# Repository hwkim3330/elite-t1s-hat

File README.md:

# Elite T1S HAT

A **10BASE-T1S** board for the **LilyGO T-ETH-Elite** (ESP32-S3), built around
the Microchip **LAN8651** MAC-PHY. It stacks on the Elite's 2×20 header and
gives it a single-pair automotive Ethernet port next to the Elite's own
100BASE-TX (W5500). This board is its own design, not a Raspberry Pi HAT on an
adapter.

**3D:** open [`mechanical/model/t1s_hat.stl`](mechanical/model/t1s_hat.stl) or
[`stack.stl`](mechanical/model/stack.stl) on GitHub to turn it in the browser.
There is also a STEP file for CAD work (`t1s_hat.step`).

| board, top | ground plane (In1) |
|---|---|
|  |  |

| folder | what |
|---|---|
| [`hardware/`](hardware/README.md) | KiCad schematic + **4-layer** PCB (Rev C; Rev B at tag `rev-b`), all generated by `make_t1s_hat.py`; gerbers; JLCPCB BOM/CPL. **[`ORDERING.md`](hardware/ORDERING.md) = how to order.** [`ELECTRICAL.md`](hardware/ELECTRICAL.md) = every value and why |
| [`firmware/`](firmware/README.md) | ESP32-S3 node firmware: LAN8651 over OPEN Alliance TC6 SPI, PLCA, ping/UDP, serial console |
| [`mechanical/`](mechanical/GEOMETRY.md) | outline, holes and header grid, measured from LilyGo's own DXF/3D (`reference/measure.py` re-derives them); `model/` has the 3D models (STL, STEP) and their build and render scripts |

## Status (2026-10-02)

| | |
|---|---|
| Design | **Rev C (4-layer) finished, ready to order**, with the pre-fabrication review fixes of 2026-10-02 (CCOMP, VDDAU, VDDA, RBIAS and crystal parts at their pins; exposed-pad paste clear of the thermal vias; see [`hardware/README.md`](hardware/README.md)). DRC 0 errors / 0 warnings, ERC 0 errors, mechanical error 0.00000 mm against `GEOMETRY.md`, 0 unrouted |
| Parts | every fitted part has an LCSC number, all in stock; **LAN8651 is the scarce one (199 at JLC, 2026-10-01)** |
| Firmware | compiles (Arduino esp32 3.3.0). It ran on a third-party LAN8651 HAT on the same pins (9.5 Mbit/s, PLCA, Zenoh); **not yet on this board, since none has been built** |
| Fabricated | **no.** Order 2–3 first, prove SPI + ping + PLCA between two nodes, then the rest |

What only a real board can settle is listed in
[`hardware/README.md`](hardware/README.md) under "What is NOT verified":
crystal oscillation margin, T1S signal quality and EMC, stack height.

## The short version of the design

- **LAN8651, single 3.3 V** from the Elite's header. The '51 regulates its own
  1.8 V core, so the board has no regulator.
- **Host SPI on the Elite's IO11/9/10, CS on IO8 (header 27), IRQ IO39,
  RESET IO42; 1PPS from DIOA4 on IO40 (header 13) and test pad TP1.** Rev C
  and the TSN Lab HAT put CS on header 24 (IO0, the BOOT strap) as a Pi HAT
  would; Rev D moved it off the strap. The firmware finds CS on either pin.
- **Bus side per AN1718:** common-mode choke → 100 nF DC block → termination
  (fit per bus position: 49R9 end / 1K5 drop) → optional ESD → 4-pin 2.54 mm push-in (Rev D)
  terminal block, wired P N N P so a node taps a daisy chain.
- **4 layers (since Rev B):** signals on top, In1 solid GND, In2 +3V3, bottom only three SPI escapes. The T1S pair is 50 Ω by construction (0.35 mm over 0.21 mm of prepreg). Rev A, the 2-layer version, is in git history.

## Where it is used

A networking test bench: ESP32-S3 nodes running Zenoh-pico behind two
TSN switches with FRER (IEEE 802.1CB). The nodes use the Elite's
own W5500 today; this HAT gives them a 10BASE-T1S edge link, and its firmware's
bridge mode joins a T1S segment to the switched 100BASE-TX backbone.

## History

Started as a sub-folder of an earlier adapter project (a Raspberry Pi HAT
carrier for the Elite) and split out on 2026-09-28 with its history, because the
board is its own product.

## License

MIT for everything written here; third-party parts keep their own licences
(listed in [`LICENSE`](LICENSE)).

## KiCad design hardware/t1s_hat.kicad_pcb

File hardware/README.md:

# T1S HAT — LAN8651 10BASE-T1S for the LilyGO T-ETH-Elite

Our own 10BASE-T1S board for the [LilyGO
T-ETH-Elite](https://github.com/Xinyuan-LilyGO/LilyGO-T-ETH-Series)
(ESP32-S3), built around a **Microchip LAN8651** MAC-PHY. It replaces buying
TSN Lab's ready-made HAT: same chip, same host header, our schematic.

Two source files govern this board and **nothing here re-derives a number in
either of them**:

| file | governs |
|---|---|
| [`ELECTRICAL.md`](ELECTRICAL.md) | every component, value and pin-handling rule, each quoted from Microchip DS60001734F or AN1718 (DS60001718D) |
| [`../mechanical/GEOMETRY.md`](../mechanical/GEOMETRY.md) | outline, mounting holes, 2×20 grid — measured from LilyGo's own DXF and 3D CAD |

Everything is generated by [`make_t1s_hat.py`](make_t1s_hat.py), which emits
the symbol library, the three project-local footprints, the schematic and the
PCB, then reads the board back and asserts every mechanical feature against
`GEOMETRY.md`.

**This is Rev D (2026-10-07): Rev C with a push-in spring terminal for the bus** -- Kefa KF141R-2.54-4P
(press the lever, push the wire in) instead of the 3.81 mm pluggable Phoenix header that needed a mating
plug. Two review bugs fixed with it:

| Rev C | Rev D | why |
|---|---|---|
| CS_N on header 24 = **IO0, the ESP32-S3's BOOT strap** | CS_N on header **27 = IO8** (free on the Elite); R5 pull-up kept | pressing BOOT on a live node asserted CS mid-transaction; any glitch on the strap at reset could also start the ROM loader |
| DIOA0…4 all to ground | **DIOA4 (pin 23) = 1PPS** to test pad **TP1** and header **13 = IO40**; DIOA0…3 still to ground | the LAN8651 has a dedicated 1PPS output on DIOA4 (PPSCTL); with DIOA grounded there was no way to see the 1588 clock on a scope, so PTP accuracy could not be measured, only precision |

PPS leaves pin 23 through a via just past its pad (F.Cu there is C4/C5 and the VDDAU lane) and runs on
B.Cu, which is empty in that area, to TP1 and the header. R5's +3V3 via moved 1 mm left to make room for
CS. DRC 0, ERC 0 errors (6 warnings, was 7: DIOA4 is no longer tied to ground), JLC CPL check exact.
Rev C is at git tag `rev-c`.

**Rev C (2026-10-01, review fixes 2026-10-02), 4-layer: the design is
finished and ready to order.** Rev C is Rev B without the status LEDs and with
VDDA rerouted; an independent review before fabrication then moved the CCOMP,
VDDAU, VDDA and RBIAS parts and the crystal next to their pins and split U1's
exposed-pad paste (see "Rev C" below). It has not been ordered yet.
Rev B is at git tag `rev-b`. Rev A was 2-layer; its layout notes (the single-layer
crossings, JP1, the 3V3 rail) are in git history before commit "Rev B".

## What it is

- **LAN8651**, 32-VQFN 5×5, single 3.3 V rail (the '51 regulates its own 1.8 V
  core, so there is no second regulator and no sequencing diode).
- **OPEN Alliance TC6 SPI** to the host on the same header pins TSN Lab's
  device-tree overlay uses, so their SDK and the mainline `microchip,lan8651`
  driver both work unmodified if this board is ever put on a Pi.
- **Bus interface network** in AN1718's MINIMAL BIN order: common-mode choke →
  AC coupling caps → termination → ESD → 4-way 2.54 mm push-in spring terminal (Rev D; Rev C: 3.81 mm pluggable)
  block, wired so the node taps a daisy chain.
- **4 layers:** signals on top, In1.Cu solid GND, In2.Cu +3V3, bottom only the
  three SPI escapes. The T1S pair is 50 Ω by construction.
- 34 parts, 4 of them deliberately unstuffed (R1/R2 termination, MOV1/MOV2 ESD).

## The two parts that had to be chosen, not assumed

Both are drawn from their own data sheet into
[`fp/t1s_hat.pretty`](fp/t1s_hat.pretty), generated by `make_t1s_hat.py`
alongside the board, and the generator asserts the pad count and the overall
land size back out of the finished `.kicad_pcb`.

### L1 — TDK **ACT1210L-201-2P-TL00**, LCSC **C131444**

AN1718 names ACT1210D-131-2P-TL00, ACT1210E-241-2P-TL00 and Murata
DLW32MH241MX2, and says in the same breath that *"exact component part numbers
and parameters must be determined by the customer's unique application
requirements"* — they are examples. All three are **3.2 × 2.5 mm** (EIA 1210)
2-line chokes in the 130…240 µH @ 100 kHz band. The board previously sat on
KiCad's `Inductor_SMD:L_CommonMode_Wurth_WE-CNSW-1206`, a **3.2 × 1.6 mm**
land: same length, 0.9 mm too narrow, so the real part's terminals miss the
pads. KiCad ships no 4-terminal common-mode choke land in 3225.

The part fitted instead is the **ACT1210L-201-2P-TL00**: same ACT1210 package,
200 µH @ 100 kHz — inside the span AN1718's own examples cover — 70 mA,
5.5 Ω, AEC-Q200, and, unlike all three examples, **stocked at LCSC**
(C131444, ~$0.39/1k), which is where this board gets built.

Its land is `t1s_hat:L_CommonMode_TDK_ACT1210_3225`, drawn from TDK's ACT1210
data sheet "Layout recommendation" (drawing IND1512-9): **4.1 mm overall
across the pads with a 2.0 mm gap between the columns**, so each pad is
1.05 mm long on a 3.05 mm pitch, and **1.6 mm overall across the rows with a
0.4 mm gap**, so each pad is 0.60 mm wide on a 1.0 mm pitch. Body from the
same sheet: 3.2 ±0.2 long, 2.5 ±0.2 wide, 3.9 max over the terminals.

The symbol changed with it: the ACT1210's windings are **1-4 and 2-3**
(pin configuration and circuit diagram, same sheet), which is
`Device:L_Coupled_1423`, not the `…_1243` the 1206 Würth part needed.

### MOV1 / MOV2 — TDK **AVRH10C221KT1R5YA8**, LCSC **C2157827**

This is the part `ELECTRICAL.md` already names, and it is a **1005 [0402]**
chip varistor — 1.0 × 0.5 × 0.5 mm, 220 V V1mA, 70 V DC, **1.5 pF**, 25 kV per
IEC 61000-4-2. The board had it on `Resistor_SMD:R_1206_3216Metric`: three
size codes too big. It is now on `t1s_hat:Varistor_TDK_AVRH10_1005`, from the
recommended land pattern in TDK's automotive AVR chip-varistor catalogue
(pad 0.35…0.45 long, gap 0.3…0.5, pad 0.4…0.6 wide — the middle of each:
**0.40 long, 0.40 gap, 0.50 wide**). KiCad's `R_0402_1005Metric` is 0.54 ×
0.64 on a 1.02 mm pitch, outside all three ranges, which is why this one is
drawn here too. Both parts stay **DNP**; the land is now a real one.

## Rev B layout — what four layers bought

| | Rev A (2-layer) | Rev B (4-layer) |
|---|---|---|
| 3V3 | a rail round three sides of the board | **In2.Cu plane**, one via beside every 3V3 pad; no 3V3 trace exists |
| GND | B.Cu pour, one via per decoupling cap | **In1.Cu plane with no tracks at all**, plus F.Cu and B.Cu pours |
| VDDP pin 17 | 84 mm lap of the board through a 0 Ω jumper (JP1) | own ferrite-option island **FB4**, 0.01 + 0.1 µF at the pin |
| VDDP pin 7 | caps 7 mm away at the end of a column | C8 then C7 straight off the pin, FB3 behind them |
| SPI | MOSI looped out to the board edge and back; MISO ran between R5's pads | 2.5 mm fan-out: MISO/CS/SCLK drop through one via each to B.Cu, MOSI/IRQ/RESET stay on F.Cu, none crosses |
| T1S pair | 0.35 mm over 1.51 mm of FR4 — nowhere near 50 Ω | 0.35 mm over 0.21 mm of prepreg — **50.1 Ω** |

The rules the layout was held to, each checked by the generator or DRC:

- **In1.Cu and In2.Cu carry no tracks** (`plane tracks: 0`). Nothing slots the
  reference plane under the pair; the only cuts are the choke void AN1718
  asks for and the antenna window.
- **Every bus trace from the choke to CN1 is 0.35 mm** (`pair width` row).
- **Nothing passes between two vias.** The QFN's 0.5 mm pitch cannot fit a
  0.45 mm via plus 0.2 mm clearance each side with a track between, so the
  three B.Cu escapes are fanned out to a 1.1 mm pitch row first.
- **The B.Cu escapes turn right at staggered heights** (9 / 10 / 11 mm) and
  enter the header between pad columns, never across one of the Elite's
  pins that this board does not use.
- **The pull-ups cost no vias of their own:** R4 and R6 sit in-line on their
  F.Cu signal, and R5 sits on the CS lane to header pin 27 (pin 24 before Rev D).

## Two decisions that are not in ELECTRICAL.md / GEOMETRY.md

### 1. No RJ45 notch — the outline is a plain rectangle

`GEOMETRY.md`'s notch exists because a board ~13 mm above the Elite would foul
the RJ45, which stands 15.97 mm. This board is lifted clear of the jack by a
taller riser instead, so nothing has to be cut away. Outline is the full
**66.22 × 49.19 mm rectangle, 3 mm corners**. Everything else mechanical in
`GEOMETRY.md` is unchanged and still authoritative: the four asymmetric
mounting holes and the 2×20 grid.

### 2. The connection is two-stage — read this before ordering parts

```
   T1S HAT  (this board)
        ↑ its 2x20 socket goes on the riser's long pins
   ── 2x20 stacking riser ──          ≈23 mm total (calculated), set by the riser
        ↑ riser socket swallows the Elite's own 9.30 mm pins
        ↑ RJ45 (15.97 mm) passes beside the stack, not through a notch
   LilyGO T-ETH-Elite (ESP32-S3)
```

**A single tall stacking header does not work here.** The Elite's pins are
only 9.30 mm long; they would reach barely halfway up a ~17 mm barrel whose
contacts sit near the top. You need a **riser** (a 2×20 stacking header that
plugs onto the Elite and presents longer pins) plus this board's **socket**.
That is a real failure mode someone will otherwise hit at the checkout page.

Board height above the Elite PCB is **≈23 mm, calculated** from the parts in
`ORDERING.md` (riser body 8.3 + ~6 mm of pin inside J1 + J1's 8.5 body), and set by the riser.
Nothing on this board depends on the exact number.

## Stack-up

JLCPCB **JLC04161H-7628**, 1.6 mm, written into the board file:

| layer | | thickness |
|---|---|---|
| F.Cu | signals, parts, GND flood | 0.035 mm (1 oz) |
| prepreg | 7628, εr 4.4 | 0.2104 mm |
| In1.Cu | **GND plane, no tracks** | 0.0152 mm (0.5 oz) |
| core | FR4 | 1.065 mm |
| In2.Cu | **+3V3 plane, no tracks** | 0.0152 mm (0.5 oz) |
| prepreg | 7628, εr 4.4 | 0.2104 mm |
| B.Cu | three SPI escapes + GND pour | 0.035 mm (1 oz) |

50 Ω single-ended on F.Cu over In1.Cu, IPC-2141:
Z0 = 87 / √(4.4 + 1.41) · ln(5.98 · 0.2104 / (0.8 · 0.35 + 0.035)) = **50.1 Ω**.
JLC's own calculator for this stack-up is the one to trust if it disagrees; ask
for impedance control when ordering and they will test it.

Design rules: 0.2 mm clearance (netclass), 0.15 mm minimum track, 0.45 mm vias
with 0.25 mm drill, 0.20 mm minimum drill (the QFN's thermal vias), and one
custom rule in `t1s_hat.kicad_dru`: **BUS_P/BUS_N keep 0.45 mm from every other
net** (pads, tracks, vias and the F.Cu flood). The one exception is inside each
MOV, whose own data-sheet land puts its BUS and GND pads 0.40 mm apart (the rule file relaxes clearance to 0.15 mm between pads inside each MOV courtyard, which covers that 0.40 mm gap).

## Termination stuffing — the one thing an assembler must decide

The board **ships with R1/R2 unstuffed**, per `ELECTRICAL.md` ("footprints
fitted, DNP by default — stuff per where this node sits on the bus"). The
silkscreen carries the table:

| where this node sits | R1, R2 |
|---|---|
| **end of the bus** | 49R9 1 % 1206 (AN1718: 1 W; the JLC variant fits 0.75 W — ORDERING.md) |
| **interior drop node** | 1K5 1 % 1206 |

`R3` (100 k) and `C3` (100 nF) — AN1718's common-mode termination — **are
fitted**. ESD elements MOV1/MOV2 have footprints and are DNP; `ELECTRICAL.md`
calls them optional.

`CN1` is wired **P N N P**, and the silkscreen carries that as a legend
(`CN1 1=P 2=N 3=N 4=P`) in the clear area to its left. Per-pad letters were
dropped: the four pads are 1.8 × 3.6 mm ovals with the connector's own body
outline 0.9 mm below them and R3/C3 0.6 mm below that, leaving a 0.6 mm slot —
nowhere to letter a pad without printing on copper. Pins 1–2 and 3–4 are the
same pair with opposite orientation, so wire P to P and N to N rather than
pin-for-pin. That order is what lets both on-board links be drawn without a
crossing.

## Verified

- **Mechanical: worst error 0.00000 mm** against `GEOMETRY.md`, tolerance
  0.01 mm, over the outline, all four mounting holes and all 40 header pads.
  `make_t1s_hat.py` prints the full table and exits non-zero on any failure.
- **Antenna keepout clean.** The generator walks every track, via, footprint
  and *filled zone polygon* on all four layers and counts anything inside
  x 58…66.22, y 22…44: **0 intruders.** The keepout is a rule area that forbids
  copper, tracks, vias, pads and footprints on all four layers, so both planes
  and both pours are cut out there. Silkscreen (ink, not copper) does mark the window.
- **In1.Cu and In2.Cu carry 0 tracks.** The T1S pair is 0.35 mm everywhere.
- **Unrouted connections: 0.**
- **L1 and MOV1/MOV2 lands read back as 4.10 × 1.60 mm on 4 pads and
  1.20 × 0.50 mm on 2 pads** — the data sheet numbers above, asserted out of
  the board file, not just written into it.
- **U1's exposed-pad paste covers no thermal via:** 12 windows, every one
  ≥ 0.15 mm off each of the nine 0.5 mm via lands, 51 % of the 3.4 mm land
  (`U1 EP paste` row).
- **ERC: 0 errors, 7 warnings** — see below.
- **DRC: 0 errors, 0 warnings, 0 unconnected** — see below.

### ERC — 0 errors

`kicad-cli` 7.0.11 has no `sch erc` subcommand, only `export`, so ERC is run
through the real eeschema on an Xvfb display by
[`run_erc.sh`](run_erc.sh), with **Show: All and Exclusions both ticked**
before the run. Report as produced: [`erc.rpt`](erc.rpt).

```
** ERC messages: 6  Errors 0  Warnings 6
```

All 6 warnings are the same thing: *"Pins of type Bidirectional and Power
output are connected"* on U1 pins 18, 19, 20, 22 (DIOA0…3) and 16, 14
(DIOB0/DIOB1). Those are the unused configurable IO tied to ground, which is
exactly what the data sheet says to do — *"When not used, these pins may be
connected directly to ground."* Nothing is excluded or suppressed.

### DRC — 0 errors, 0 warnings

Run through `pcbnew.WriteDRCReport()` (same engine; `kicad-cli` has no
`pcb drc` either). Report as produced: [`drc.rpt`](drc.rpt).

```
** Found 0 DRC violations **
** Found 0 unconnected pads **
** Found 0 Footprint errors **
```

No clearance, hole, courtyard, keepout, solder-mask, silkscreen, unconnected-pad
or library-consistency finding. (The four mounting holes used to raise
`lib_footprint_issues`; their footprint is now written into the project library by
the generator itself, so the board copy and the library copy cannot differ.)
Nothing is excluded. Running it yourself reproduces exactly this.

## Inferences — things not taken from the spec files

Flagged because they are judgement, not quotation:

1. **U1 pin 1 (INH) is left unconnected.** `ELECTRICAL.md`'s pin-handling
   table does not cover INH. DS60001734F Table 3-5 says *"When not used, this
   pin should be left unconnected"*, so it is, with no copper stub.
2. **L1 is a 200 µH part where AN1718's examples are 130 and 240 µH.**
   AN1718 gives no minimum or maximum, only three example part numbers and an
   instruction to pick for the application; 200 µH is inside the span they
   cover and is the value TDK itself lists for one-pair automotive Ethernet.
   The land pattern is quoted, not inferred — but the *choice of value inside
   that span* is judgement.
3. **VDDP is split into two ferrite-option islands**, `VDDP` (pin 7, with
   TEST) on FB3 and `VDDP_17` (pin 17) on FB4. Both are fed from the same
   +3V3 plane, and with the default 0 Ω beads they are the same supply.
   `ELECTRICAL.md` asks for the bead option per supply; one per pin is the
   layout choice that keeps each pin's decoupling at the pin.
4. **The crystal is a 4-pad 3225, YXC X322525MOB4SI (C9006), CL 12 pF.**
   Until 2026-09-28 the board used a 2-pad 3.2 × 1.5 mm land. That was wrong:
   no 25 MHz crystal is made in that package, so the land matched no part.
   CL 12 pF rather than 18 pF is deliberate: 18 pF caps in series plus ~3 pF
   stray present 12 pF. Each lid pad (2, 4) has its own ground via; pad 2's is
   shared with R7's ground end beside it. Reasoning and margin numbers are in `ELECTRICAL.md`,
   "Clock".
5. **XTI is declared `passive` in the LAN8651 symbol**, not `input`. It is an
   oscillator pin driven by a passive crystal; declaring it an input makes
   KiCad's `pin_not_driven` test fire on a net that has no driver by design.
   Common practice, but it is a choice.
6. **The 40-pin header is a project-local symbol**, `t1s_hat:HAT_HEADER_2x20`,
   not `Connector_Generic:Conn_02x20_Odd_Even`. Its pins carry real electrical
   types (the six host signals are `output`/`input`, everything else
   `passive`), because the ESP32 side really is the driver and the generic
   connector's all-passive pins make ERC report every SPI input as undriven.
   The **footprint** is the stock `PinHeader_2x20_P2.54mm_Vertical`.
7. **Header pin 1 is at the USB-C (high-x) end, odd pins on the inner row
   (y = 5.900).** Rev A and early Rev B had this backwards (pin 1 at the low-x
   end on the edge row), inferred rather than measured. That was the exact
   180° opposite, and it would have put HAT GND on the Elite's 5 V. It is now
   taken from LilyGo's own pin-map image, cross-checked against the hole
   asymmetry and the antenna position (`../mechanical/GEOMETRY.md`), and
   asserted by the generator independently of `pin_xy()`: pin 1 must be the
   highest-x pad and on the inner row.
8. **`BIN_VOID` = x 21…40.5, y 23.4…39.8** and **`CMC_VOID` = x 26.90…30.10,
   y 24.40…28.80.** AN1718 asks for "a void in the ground flooding on the
   outside layer surrounding the BIN" and "an all-layer void underneath the
   CMC" **without giving dimensions**, so both sizes are judgement. The first
   follows the BIN components. The second is the only place other than the
   antenna window where the ground plane is cut, so it is sized to the
   part and no further: **the ACT1210's maximum body — 3.9 mm over the
   terminals × 2.7 mm wide (2.5 + tolerance) — plus 0.25 mm a side**, giving
   3.2 × 4.4 mm (L1 is rotated 90°, so the 3.9 runs along y). The margin
   covers placement tolerance and nothing else; the body is what couples to
   the plane, because the body is the core. That also covers the 4.1 × 1.6 mm
   land with room to spare. The void grew in x against the old number above,
   not because the margin grew but because the part did: the 1206 land it used
   to be sized around was the wrong part. Nothing but L1's own nets crosses it
   on any layer; VDDA passes on B.Cu 0.45 mm below it.
9. **The T1S pair necks to 0.15 mm at the QFN.** The package puts TRXP and
   TRXN 0.5 mm apart; AN1718's "3× trace width centre-to-centre to other
   signals" cannot be met between the pair's own two legs at a 0.5 mm-pitch
   QFN, and Microchip's own EVB does not either. It **is** met against every
   other net, by the F.Cu void around the BIN.
10. **Pair length match ≈0.2 mm.** TRXN opens out to the choke before TRXP
    does (so the gap only ever grows), which costs about 0.2 mm of mismatch —
    roughly 1.2 ps. Not measured on hardware.
11. **The stackup numbers** are JLCPCB's published JLC04161H-7628 build,
    taken as given, not measured. The 50 Ω figure follows from them.

## Files

| file | what |
|---|---|
| `ELECTRICAL.md` | **electrical source of truth** |
| [`ORDERING.md`](ORDERING.md) | **JLCPCB order: options, parts, what to hand-solder, what to check in the preview** |
| `jlcpcb/bom_jlc.csv` / `cpl_jlc.csv` | assembly files in JLC's column format, fitted SMT/THT parts only |
| [`../firmware/`](../firmware/README.md) | ESP32-S3 bring-up / node firmware (LAN8651 over TC6 SPI, PLCA, console) |
| `make_t1s_hat.py` | generator: symbol lib → schematic → PCB → verify → DRC → exports |
| `run_erc.sh` | runs eeschema's ERC headlessly (Xvfb + xdotool) and saves the report |
| `fill_zones.sh` | fills the zones through pcbnew's GUI — `ZONE_FILLER` segfaults in KiCad 7.0.11's Python bindings |
| `t1s_hat.kicad_sch` / `.kicad_pro` / `sym-lib-table` / `fp-lib-table` | schematic + project |
| `sym/t1s_hat.kicad_sym` | **LAN8651** (33 pins incl. the exposed pad) and the host header — neither exists in KiCad's libraries |
| `fp/t1s_hat.pretty/` | the TDK ACT1210 choke land and the TDK AVRH10 varistor land, each from that part's own data sheet — KiCad ships neither — and U1's QFN: KiCad's TQFN-32 5×5 with its exposed-pad paste split clear of the thermal vias |
| `t1s_hat.kicad_dru` | the custom DRC rule for the bus pair (written by the generator) |
| `t1s_hat.kicad_pcb` | the board |
| `gerbers/t1s_hat_gerbers.zip` | fab-ready: 10 gerber layers (4 copper), separate PTH/NPTH Excellon, drill maps, job file |
| `bom.csv` / `cpl.csv` | BOM (with a `Populate` column) and position file |
| `preview-front/back/in1/in2.png` (+ `.svg`) | all four copper layers |
| `erc.rpt` / `drc.rpt` | reports as produced, nothing excluded |

Regenerate with `python3 make_t1s_hat.py`. Geometry is reproducible to the
internal unit, but the output is not byte-reproducible — KiCad stamps fresh
UUIDs and timestamps on every run. Compare the printed coordinate table, not
the files.

Drill files and `cpl.csv` are plotted against the drill/place origin, which the
generator puts on `GEOMETRY.md`'s own origin, so `NPTH.drl` literally reads
`X3.33Y4.63` and `cpl.csv` reads `8.196, 3.360`.

## Bottom side

The board sits ~23 mm above the Elite. The J1 socket body occupies y 0…9 on
the bottom, and B.Cu carries only the three SPI escapes between the QFN and the
header. Everything else on the bottom is GND pour. Over the Elite's RJ45
(x −5.18…16.42, y 10.50…28.90) the clearance below is much less than
elsewhere, since the jack tops out at 15.17 mm above the Elite's PCB.

## Review notes (2026-09-29)

An external review of Rev B raised these; each was checked against the board
file and Microchip's documents before anything changed.

| point | finding | action |
|---|---|---|
| BUS_P 37.7 mm vs BUS_N 21.9 mm | True totals, but the **node's own stub is 15.92 mm on both**. The difference is the through-bus between CN1's two halves (18.1 vs 3.8 mm): ≈93 ps of skew against an 80 ns symbol, ≈ −43 dB mode conversion at 25 MHz. | Kept. The suggested "P N" in + "P N" out needs the pair to cross (vias in the bus network); the mirrored **P N N P** is what makes both links routable on one layer. |
| CCOMP "metal film" | Correct: the data sheet's body (DS60001734F) and the checklist both say "4.7 µF low ESR (metal film)"; only the pin table says "low ESR". *(An earlier version of this table said the data sheet does not — that was wrong.)* | C4 X5R → **X7R**, recorded in `ELECTRICAL.md` as a **non-compliant prototype choice** to verify on the first boards. |
| Ferrite islands need local 10 µF | Correct per the checklist, **only if a bead is fitted**. | FB1–4 documented as 0 Ω links; with 0 Ω the single C6 is compliant. |
| Test points for SPI/IRQ/RESET/3V3/GND | All eight are already adjacent J1 pads (pins 15–24), accessible from the top. | **Labelled** on the silkscreen instead of adding copper to the signal paths. |
| Series-R footprints on SCLK/MOSI | Series damping belongs at the **driver**. SCLK/MOSI are driven by the ESP32, on the Elite, not here. | Not added. The firmware lowers the ESP32's drive strength instead; MISO's driver (LAN8651) has its own pad-drive setting (PADCTRL). |
| 0.15 mm neck at the QFN | The pads are 0.25 mm wide on a 0.5 mm pitch, so the neck is the escape itself (TRXP 2.74 mm, TRXN 2.95 mm total). | Kept. |
| Stack height 18–20 vs 23 mm | Stale text in three files. | Fixed: ≈23 mm (calculated) throughout. |
| Antenna keepout | — | Unchanged. It is empty on purpose. |

## Rev C (current) — what changed from Rev B, and why

Rev B is kept, as designed (never ordered), at the git tag **`rev-b`**. Rev C changes only what the
bench and the data sheet showed was wrong, and it gets cheaper doing it.

| change | why |
|---|---|
| **Status LEDs D1/D2 and R8/R9 removed; DIOA0/1 to ground** | the LAN8651 has **no LED function**: PADCTRL A0SEL/A1SEL offer only event capture / event generator (DS60001734F §11.6.3), so Rev B's LEDs could never have shown PLCA state. Status is on the Elite's own LED (IO38), driven by firmware: solid = beacons seen, fast blink = no beacons, slow blink = no link. **Four parts fewer, two of them extended** (two JLC setup fees) |
| **VDDA leaves pin 29 through two vias** | Rev B ran it along the outermost top lane, 0.25 mm inside the choke's maximum outline. It now drops to B.Cu beside the pin, below the CMC void, and rises again at C12 (since the 2026-10-02 review fixes, at the top-left corner of U1; see below). The verifier's VDDA exception is gone: **nothing but L1's own nets crosses the void, on any layer** |
| silkscreen "REV C" | |

### Rev C review fixes (2026-10-02)

An independent review of the Rev C layout, before anything was ordered. Each
item was checked against the board file; distances are pad centre to pad
centre, lengths are routed copper.

| change | why |
|---|---|
| **C4 (CCOMP 4.7 µF) next to pin 21:** 6.1 → 2.9 mm, C5 2.3 → 1.4 mm; the trace is 0.30 / 0.40 mm (was 0.15) and 3.0 mm long (was 10.1); each cap has its own ground via | the core LDO's compensation was 10 mm of 0.15 mm trace away. DIOA0…4 now tie inward to the exposed pad, which freed the right edge of U1 |
| **U1 exposed-pad paste split into 12 windows clear of the 9 thermal vias** (51 % coverage, ≥ 0.15 mm off every via land); land, mask and vias unchanged | KiCad's stock paste squares covered the four corner vias, so solder would wick down them. The footprint is now a project-local copy (`…_SplitPaste`) |
| **C14/C13 (VDDAU) at pin 25:** 15.4 / 15.8 → 2.1 / 2.6 mm; FB2 behind them | pin 25's decoupling was 18 mm along a 0.15 mm trace |
| **C12/C11 (VDDA) moved to the top-left corner of U1:** pin to C12 7.1 → 5.0 mm of copper | still two vias and a B.Cu hop (pin 29 has the choke void above it and the crystal lanes to its right); the hop now passes under the TRXP/TRXN escapes, 0.45 mm below the void, with the In1 ground plane between |
| **R7 (RBIAS) on end beside pin 26:** 10.4 → 1.6 mm, trace 13.3 → 1.8 mm. RBIAS now runs within 0.6 mm of XTI for 1.4 mm (was ≈10 mm in parallel lanes 0.5 mm apart) | the bias resistor sat at the far end of a lane beside XTI. The crystal lanes now cross R7's grounded end and its via, never its RBIAS end |
| **Y1, C15, C16 closer:** XTI 15.7 → 10.0 mm, XTO 8.3 → 8.5 mm. Y1 is turned 270°; XTI runs between its pad rows to pad 3, each lid pad has its own via | XTI used to go out past the crystal and come back. XTO's length is unchanged because, as the outermost pin, it has to climb past R7; it keeps 0.2 mm from the choke void's edge |
| **Bus spacing enforced by DRC:** custom rule BUS_P/BUS_N ↔ any other net ≥ 0.45 mm. The two bus lanes moved 0.15 mm (to clear R1/R2's centre-tap pads) and the MOV stubs end on the near half of their pads | the generator's comment claimed this rule (and a 2-layer board); neither was true, and its net-class table never reached the board. The classes now carry the board's real 0.2 mm and survive the save |
| **Silkscreen at J1: "PIN 1 = USB-C END" and "TURNED 180 = GND ON 5V"** | the socket goes on either way round, and turned 180° it puts this board's GND (pin 39) on the Elite's 5 V (pin 2) |
| `erc.rpt` regenerated (it was from Rev B); oscillator gm corrected in `ELECTRICAL.md` | DS60001734F §8.6 does give the gm: 18.2 mS nominal, ≈16× the crystal's 1.1 mA/V |

Three designators (C5, C14, R7) are left off the silkscreen: there is no free
spot beside them that would not read as a neighbour's. They are in `bom.csv`,
`cpl.csv` and the assembly files as usual.

Considered and **not** done, on purpose:

- **A node-ID DIP / a termination switch.** Physical switches cost money and space,
  and a bench or harness node is configured once. ID and count stay in firmware
  (console + NVS, settable over Zenoh); termination stays a choice at order time
  (`jlcpcb/end/` vs `drop/`), and the 1206 parts are easy to hand-fit later.
- **A metal-film CCOMP.** No 4.7 µF film capacitor exists in SMD at JLC (only
  ≥ 22.5 mm-pitch through-hole). C4 stays X7R; the LAN8651 HAT that ran at line
  rate on the bench (9.5 Mbit/s, 0 loss) is the evidence it works.
- **Separate 1 mm test pads.** J1's pads are labelled probe points with GND beside
  them; adding stubs to the SPI lines buys little.

Measured with a LAN8651 HAT on this firmware (2026-10-01): SPI 25 MHz asked (26.67 MHz actual) → 9.0 Mbit/s
PC → node without loss, 9.5 node → PC, ping 0.85 ms; with PLCA no node-side loss in
any contention test, where CSMA/CD lost up to 27 %. Full report and the design
lessons behind Rev C: <https://github.com/hwkim3330/t1s-eval>.

### Bring-up order for the first boards

1. Power: 3.3 V rail, then **CCOMP ≈1.8 V** (level and ripple — the X7R check)
2. SPI: DEVID read (MMS10 0x94)
3. RESET and IRQ lines
4. T1S link up — the Elite's LED goes solid once PLCA beacons are seen
5. PLCA, node 0 and node 1
6. Ping
7. UDP throughput — 9 Mbit/s each way at SPI 25 MHz asked (26.67 actual) is what the reference reached
8. Zenoh (build with `-DT1S_WITH_ZENOH`)
9. Scope TRXP/TRXN at the connector

**Still a prototype build:** C4 is X7R where Microchip asks for metal film, R1/R2
are 0.75 W where AN1718 lists 1 W, and L1 is a 200 µH choke outside AN1718's named
examples. Each is documented in `ELECTRICAL.md`.

Next step after this HAT: a standalone T1S node board (ESP32-S3 + LAN8651 + USB-C
on one PCB, no stacking), running Zenoh on the node itself.

## What is NOT verified — read before ordering

- **This PCB has not been built.** The firmware and the measurements ran on T-ETH-Elite boards with a third-party LAN8651 HAT on a 2×20 riser (see `firmware/README.md`), not on this board.
- **The two project-local lands come from data sheets, and have now been
  cross-checked against a second, independent source.** L1 was drawn from TDK's
  ACT1210 layout recommendation, MOV from TDK's AVR catalogue. On 2026-10-01 both
  were compared with the EasyEDA footprints JLC places for those LCSC numbers. **L1:**
  same pitch (1.0 × 3.05 vs 3.15 mm), same width (0.60 mm) and the same 2.0 mm inner
  gap; JLC's pads are 0.10 mm longer at the outer toe (1.15 vs 1.05 mm). That is
  solder-fillet margin, not a placement error, and `check_jlc_cpl.py` puts every pad
  within 0.15 mm. **MOV:** JLC only has a generic R0402 land (0.57 × 0.54 mm,
  0.87 mm pitch); ours is TDK's own (0.40 × 0.50 mm, 0.80 mm pitch). The MOVs are
  hand-fitted, so ours is the one that counts.
- **Stock was read on 2026-10-01 from JLC's own assembly warehouse, not ordered
  against.** All 15 lines of the `end/` BOM are in stock. The scarce one is **U1, LAN8651B1-E/LMX
  (C22386973): 199 at JLC.** Check it first. LCSC retail shows R4–R6 (10k 0603,
  C25804) at 0, but that is LCSC's shop. JLC assembles from its own stock, which
  has 23 million.
- **The pair's 50 Ω is calculated, not measured.** Order JLC impedance
  control if you want it tested. T1S signal quality and EMC need a built board.
- **Oscillator margin is computed from a nominal figure.** The crystal needs
  gm_crit ≈ 1.1 mA/V; DS60001734F §8.6 gives the LAN8651's oscillator
  transconductance as 18.2 mS nominal, a margin of ≈16. Nominal is not a
  guaranteed minimum, so check it on the first board (`ELECTRICAL.md`, "Clock").
- **The riser stack height (≈23 mm) is calculated, not measured.** Nothing on the
  board depends on the exact value, but the standoffs do: measure one stack first.
- **No order was placed.** The deliverable is fab-ready files to upload.

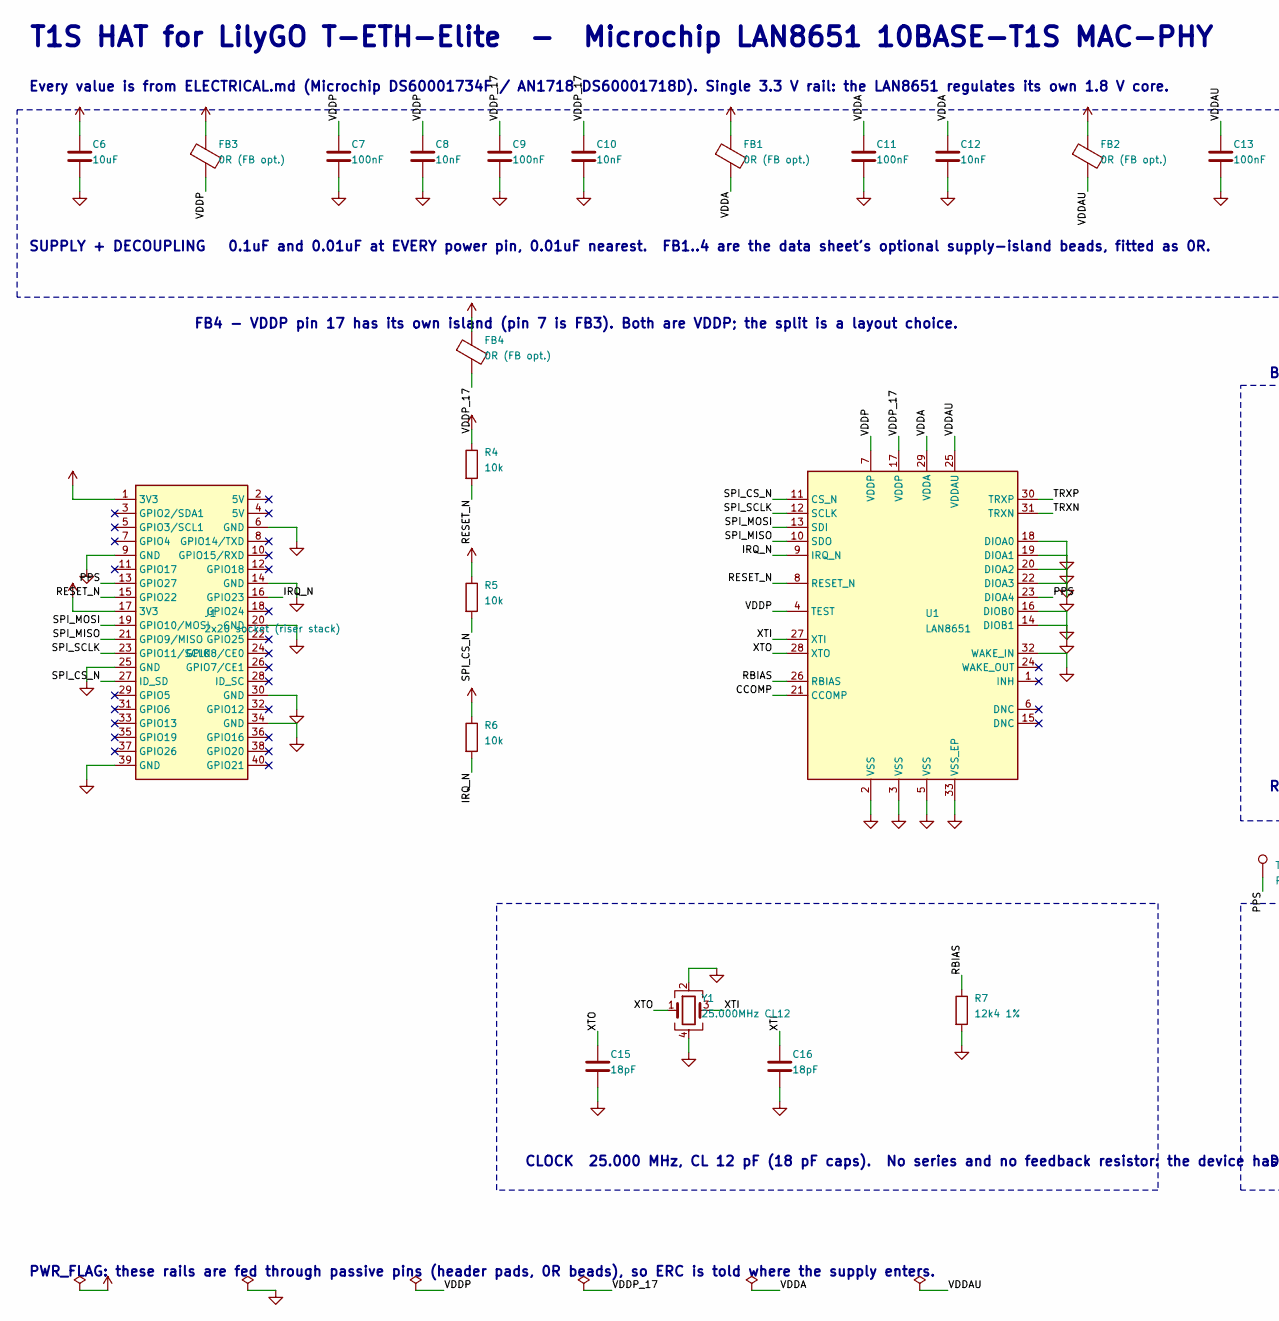
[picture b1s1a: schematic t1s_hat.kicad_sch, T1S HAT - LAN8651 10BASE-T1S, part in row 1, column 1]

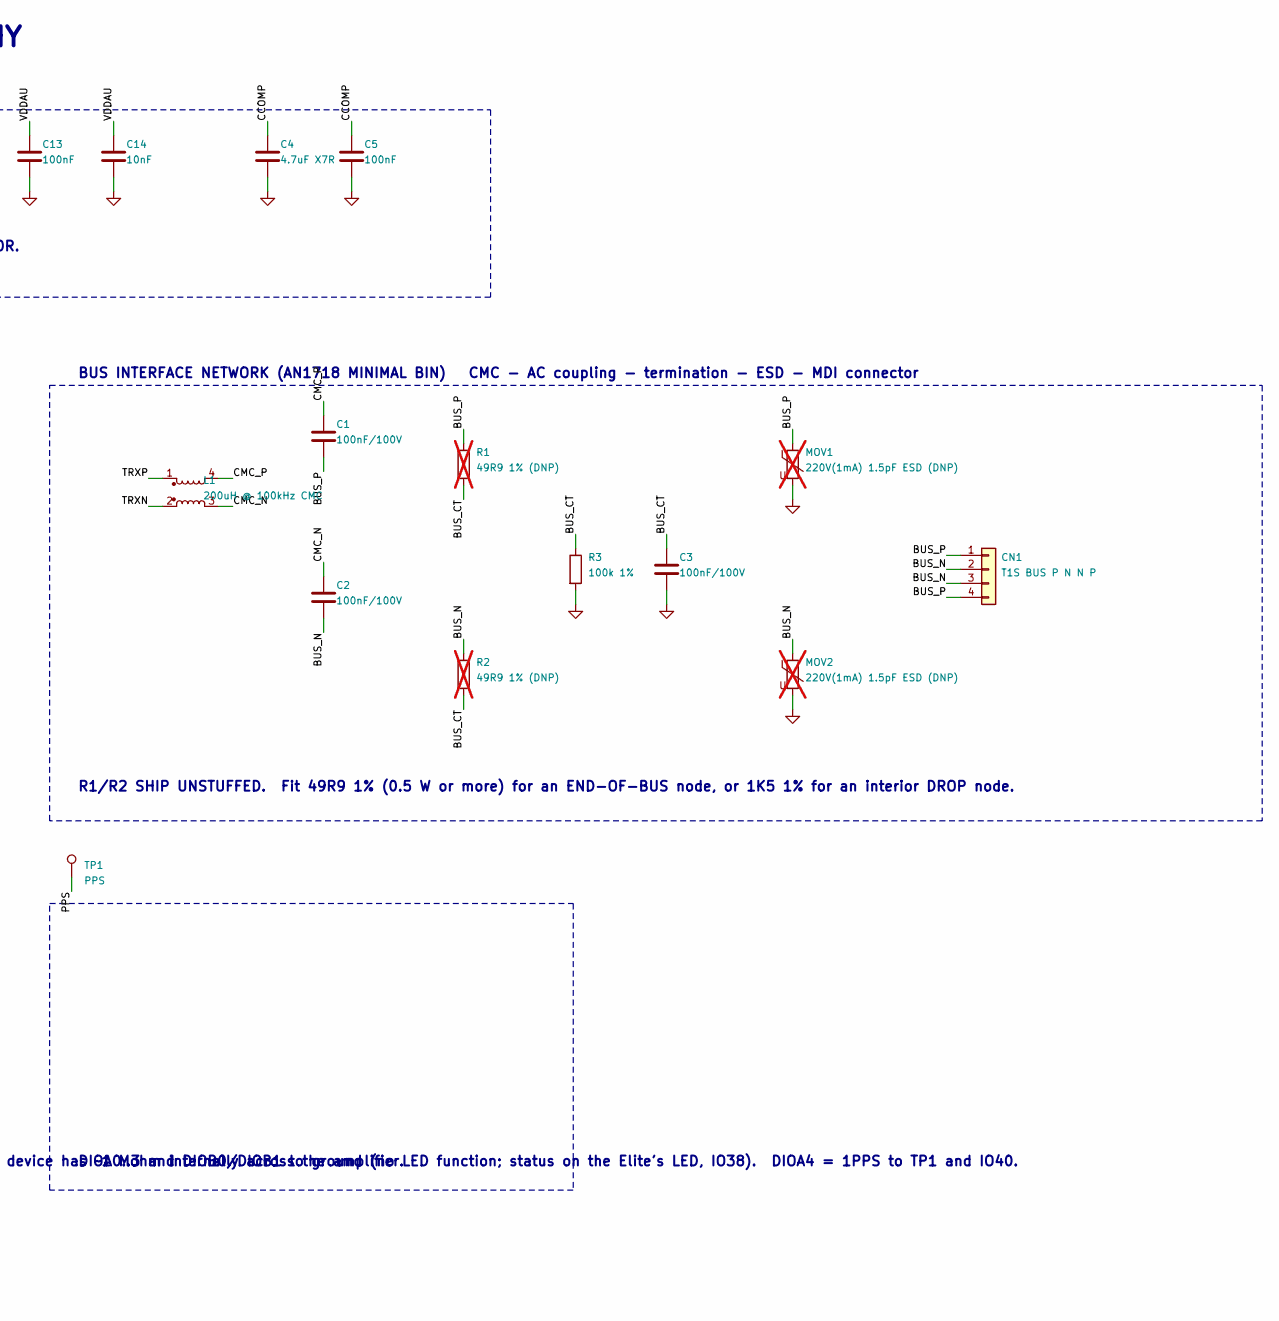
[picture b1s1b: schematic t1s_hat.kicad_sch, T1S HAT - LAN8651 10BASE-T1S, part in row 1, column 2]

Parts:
C1, C2, C3: 100nF/100V; C_0805_2012Metric; LCSC C28233
C4: 4.7uF X7R; C_0805_2012Metric; LCSC C354262
C5, C7, C9, C11, C13: 100nF; C_0603_1608Metric; LCSC C14663
C6: 10uF; C_0805_2012Metric; LCSC C15850
C8, C10, C12, C14: 10nF; C_0603_1608Metric; LCSC C57112
C15, C16: 18pF; C_0603_1608Metric; LCSC C1647
CN1: T1S BUS P N N P; TerminalBlock_Kefa_KF141R-2.54-4P; LCSC C475126
FB1, FB2, FB3, FB4: 0R (FB opt.); L_0603_1608Metric; LCSC C21189
J1: 2x20 socket (riser stack); PinHeader_2x20_P2.54mm_Vertical
L1: 200uH @ 100kHz CMC; L_CommonMode_TDK_ACT1210_3225; LCSC C131444
MOV1, MOV2: 220V(1mA) 1.5pF ESD (DNP); Varistor_TDK_AVRH10_1005; LCSC C2157827; not fitted
R1, R2: 49R9 1% (DNP); R_1206_3216Metric; LCSC C4014562; not fitted
R3: 100k 1%; R_0805_2012Metric; LCSC C149504
R4, R5, R6: 10k; R_0603_1608Metric; LCSC C25804
R7: 12k4 1%; R_0603_1608Metric; LCSC C22865
TP1: PPS; TestPoint_Pad_D1.5mm
U1: LAN8651; TQFN-32-1EP_5x5mm_P0.5mm_EP3.4x3.4mm_ThermalVias_SplitPaste; LCSC C22386973
Y1: 25.000MHz CL12; Crystal_SMD_3225-4Pin_3.2x2.5mm; LCSC C9006

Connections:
+3V3: C6.1, FB1.1, FB2.1, FB3.1, FB4.1, J1.1 (3V3), J1.17 (3V3), R4.1, R5.1, R6.1
BUS_CT: C3.1, R1.2, R2.2, R3.1
BUS_N: C2.2, CN1.2, CN1.3, MOV2.1, R2.1
BUS_P: C1.2, CN1.1, CN1.4, MOV1.1, R1.1
CCOMP: C4.1, C5.1, U1.21 (CCOMP)
CMC_N: C2.1, L1.3
CMC_P: C1.1, L1.4
GND: C3.2, C4.2, C5.2, C6.2, C7.2, C8.2, C9.2, C10.2, C11.2, C12.2, C13.2, C14.2, C15.2, C16.2, J1.6 (GND), J1.9 (GND), J1.14 (GND), J1.20 (GND), J1.25 (GND), J1.30 (GND), J1.34 (GND), J1.39 (GND), MOV1.2, MOV2.2, R3.2, R7.2, U1.2 (VSS), U1.3 (VSS), U1.5 (VSS), U1.14 (DIOB1), U1.16 (DIOB0), U1.18 (DIOA0), U1.19 (DIOA1), U1.20 (DIOA2), U1.22 (DIOA3), U1.32 (WAKE_IN), U1.33 (VSS_EP), Y1.2, Y1.4
IRQ_N: J1.16 (GPIO23), R6.2, U1.9 (IRQ_N)
PPS: J1.13 (GPIO27), TP1.1, U1.23 (DIOA4)
RBIAS: R7.1, U1.26 (RBIAS)
RESET_N: J1.15 (GPIO22), R4.2, U1.8 (RESET_N)
SPI_CS_N: J1.27 (ID_SD), R5.2, U1.11 (CS_N)
SPI_MISO: J1.21 (GPIO9/MISO), U1.10 (SDO)
SPI_MOSI: J1.19 (GPIO10/MOSI), U1.13 (SDI)
SPI_SCLK: J1.23 (GPIO11/SCLK), U1.12 (SCLK)
TRXN: L1.2, U1.31 (TRXN)
TRXP: L1.1, U1.30 (TRXP)
VDDA: C11.1, C12.1, FB1.2, U1.29 (VDDA)
VDDAU: C13.1, C14.1, FB2.2, U1.25 (VDDAU)
VDDP: C7.1, C8.1, FB3.2, U1.4 (TEST), U1.7 (VDDP)
VDDP_17: C9.1, C10.1, FB4.2, U1.17 (VDDP)
XTI: C16.1, U1.27 (XTI), Y1.3
XTO: C15.1, U1.28 (XTO), Y1.1

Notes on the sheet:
T1S HAT for LilyGO T-ETH-Elite - Microchip LAN8651 10BASE-T1S MAC-PHY
Every value is from ELECTRICAL.md (Microchip DS60001734F / AN1718 DS60001718D). Single 3.3 V rail: the LAN8651 regulates its own 1.8 V core.
SUPPLY + DECOUPLING 0.1uF and 0.01uF at EVERY power pin, 0.01uF nearest. FB1..4 are the data sheet's optional supply-island beads, fitted as 0R.
FB4 - VDDP pin 17 has its own island (pin 7 is FB3). Both are VDDP; the split is a layout choice.
BUS INTERFACE NETWORK (AN1718 MINIMAL BIN) CMC - AC coupling - termination - ESD - MDI connector
R1/R2 SHIP UNSTUFFED. Fit 49R9 1% (0.5 W or more) for an END-OF-BUS node, or 1K5 1% for an interior DROP node.
CLOCK 25.000 MHz, CL 12 pF (18 pF caps). No series and no feedback resistor: the device has ~1 Mohm internally across the amplifier.
DIOA0..3 and DIOB0/DIOB1 to ground (no LED function; status on the Elite's LED, IO38). DIOA4 = 1PPS to TP1 and IO40.
PWR_FLAG: these rails are fed through passive pins (header pads, 0R beads), so ERC is told where the supply enters.

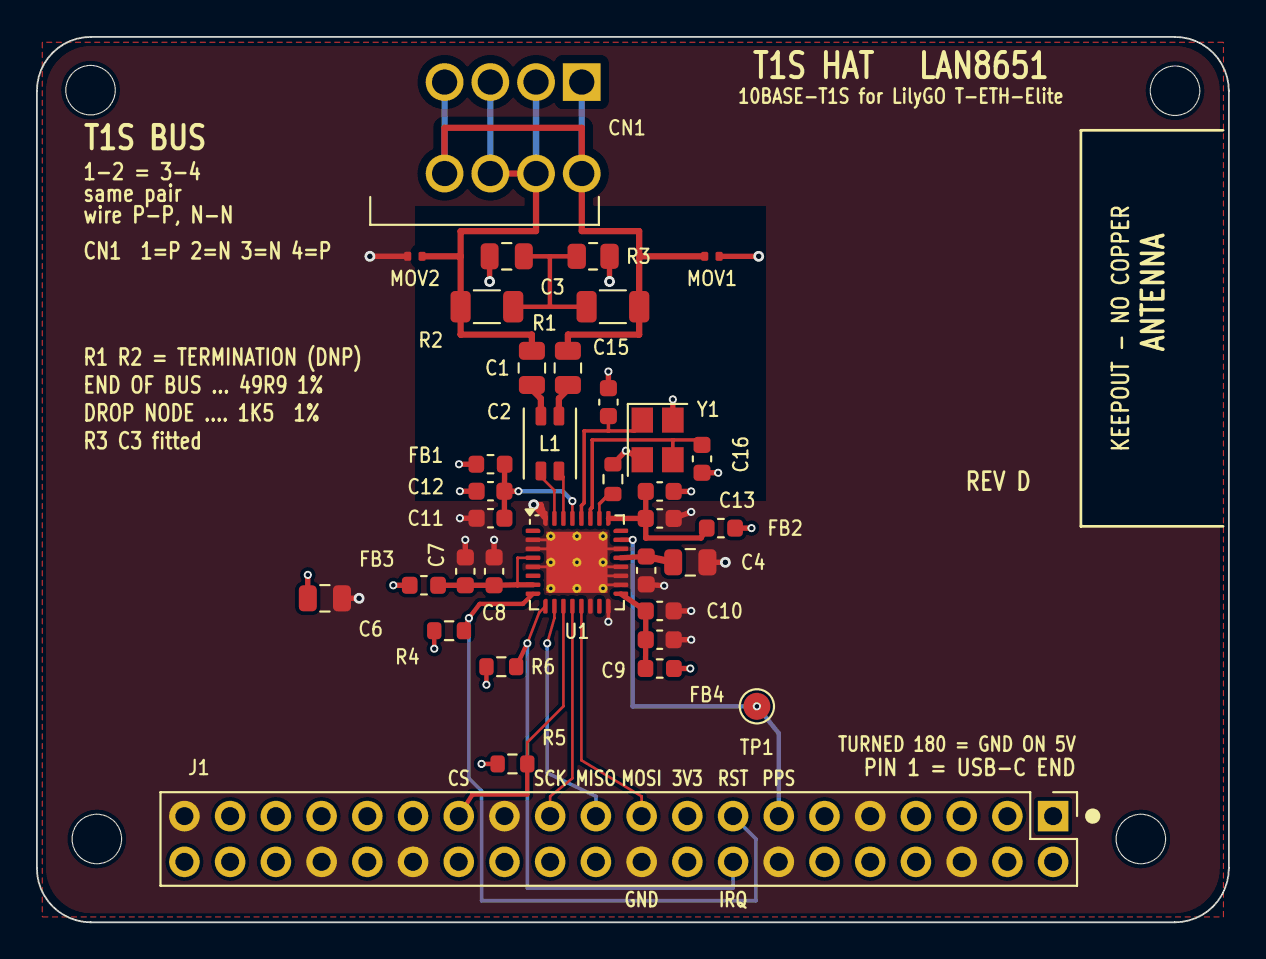
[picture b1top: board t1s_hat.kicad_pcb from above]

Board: 4 copper layers, 66.2 x 49.2 mm, 39 parts (0 on the bottom side), 24 nets.

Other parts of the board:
H1, H2, H3, H4: NPTH_2.75mm

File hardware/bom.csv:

Comment,Designator,Footprint,Quantity,Populate,Description,LCSC
100nF/100V,C1,Capacitor_SMD:C_0805_2012Metric,1,fit,"AC coupling / galvanic isolation, bus P. ALWAYS FITTED (AN1718)",C28233
10nF,C10,Capacitor_SMD:C_0603_1608Metric,1,fit,"VDDP (pin 17) decoupling, 0.01 uF - closest to the pin",C57112
100nF,C11,Capacitor_SMD:C_0603_1608Metric,1,fit,"VDDA (pin 29) decoupling, 0.1 uF",C14663
10nF,C12,Capacitor_SMD:C_0603_1608Metric,1,fit,"VDDA (pin 29) decoupling, 0.01 uF - closest to the pin",C57112
100nF,C13,Capacitor_SMD:C_0603_1608Metric,1,fit,"VDDAU (pin 25) decoupling, 0.1 uF",C14663
10nF,C14,Capacitor_SMD:C_0603_1608Metric,1,fit,"VDDAU (pin 25) decoupling, 0.01 uF - closest to the pin",C57112
18pF,C15,Capacitor_SMD:C_0603_1608Metric,1,fit,Crystal load capacitor C1 (data sheet: C1 = C2 = 18 pF),C1647
18pF,C16,Capacitor_SMD:C_0603_1608Metric,1,fit,Crystal load capacitor C2 (data sheet: C1 = C2 = 18 pF),C1647
100nF/100V,C2,Capacitor_SMD:C_0805_2012Metric,1,fit,"AC coupling / galvanic isolation, bus N. ALWAYS FITTED (AN1718)",C28233
100nF/100V,C3,Capacitor_SMD:C_0805_2012Metric,1,fit,"Common-mode termination, centre tap to ground (AN1718 C3)",C28233
4.7uF X7R,C4,Capacitor_SMD:C_0805_2012Metric,1,fit,"CCOMP: internal +1.8 V core LDO compensation. REQUIRED, low ESR, to the ground plane (LAN8651 only). Microchip asks for metal film; X7R MLCC here is a prototype deviation, see ELECTRICAL.md.",C354262
100nF,C5,Capacitor_SMD:C_0603_1608Metric,1,fit,"CCOMP support capacitor (data sheet: useful, not required)",C14663
10uF,C6,Capacitor_SMD:C_0805_2012Metric,1,fit,Bulk decoupling on the 3.3 V supply side,C15850
100nF,C7,Capacitor_SMD:C_0603_1608Metric,1,fit,"VDDP (pin 7) decoupling, 0.1 uF",C14663
10nF,C8,Capacitor_SMD:C_0603_1608Metric,1,fit,"VDDP (pin 7) decoupling, 0.01 uF - closest to the pin",C57112
100nF,C9,Capacitor_SMD:C_0603_1608Metric,1,fit,"VDDP (pin 17) decoupling, 0.1 uF",C14663
T1S BUS  P N N P,CN1,t1s_hat:TerminalBlock_Kefa_KF141R-2.54-4P,1,fit,"MDI connector, 4-pin 2.54 mm push-in spring terminal (lever). Pins 1..4 = P N N P; the two P and the two N are shorted on board so the node taps a daisy chain.",C475126
0R (FB opt.),FB1,Inductor_SMD:L_0603_1608Metric,1,fit,VDDA supply island option: 0 ohm fitted. A real bead needs a local 10 uF after it (DS60001746D); may be replaced by a ~300 ohm @ 100 MHz bead (e.g. Wuerth 742792640).,C21189
0R (FB opt.),FB2,Inductor_SMD:L_0603_1608Metric,1,fit,VDDAU supply island option: 0 ohm fitted. A real bead needs a local 10 uF after it (DS60001746D).,C21189
0R (FB opt.),FB3,Inductor_SMD:L_0603_1608Metric,1,fit,VDDP (pin 7) supply island option: 0 ohm fitted. A real bead needs a local 10 uF after it (DS60001746D).,C21189
0R (FB opt.),FB4,Inductor_SMD:L_0603_1608Metric,1,fit,VDDP (pin 17) supply island option: 0 ohm fitted. A real bead needs a local 10 uF after it (DS60001746D).,C21189
2x20 socket (riser stack),J1,Connector_PinHeader_2.54mm:PinHeader_2x20_P2.54mm_Vertical,1,fit,2x20 2.54 mm THT socket; mates with the riser that plugs onto the T-ETH-Elite's own 9.30 mm header pins,
200uH @ 100kHz CMC,L1,t1s_hat:L_CommonMode_TDK_ACT1210_3225,1,fit,"Common-mode choke, 2-line, 200 uH @ 100 kHz, EIA 1210 (3.2x2.5 mm), AEC-Q200 - TDK ACT1210L-201-2P-TL00 (AN1718 L1). ALWAYS FITTED.",C131444
220V(1mA) 1.5pF ESD (DNP) [DNP],MOV1,t1s_hat:Varistor_TDK_AVRH10_1005,1,DNP,"ESD element on bus P, at the connector (AN1718 MOV1) - TDK AVRH10C221KT1R5YA8 chip varistor, 1005 [0402], 1.5 pF. Optional.",C2157827
220V(1mA) 1.5pF ESD (DNP) [DNP],MOV2,t1s_hat:Varistor_TDK_AVRH10_1005,1,DNP,"ESD element on bus N, at the connector (AN1718 MOV2) - TDK AVRH10C221KT1R5YA8 chip varistor, 1005 [0402], 1.5 pF. Optional.",C2157827
49R9 1% (DNP) [DNP],R1,Resistor_SMD:R_1206_3216Metric,1,DNP,"Bus termination, P leg. 49R9 1% for an END node (AN1718: 1 W; the orderable part is 0.75 W, see ORDERING.md), 1K5 1% for a DROP node. Shipped unstuffed - see README.",C4014562
49R9 1% (DNP) [DNP],R2,Resistor_SMD:R_1206_3216Metric,1,DNP,"Bus termination, N leg. 49R9 1% for an END node (AN1718: 1 W; the orderable part is 0.75 W, see ORDERING.md), 1K5 1% for a DROP node. Shipped unstuffed - see README.",C4014562
100k 1%,R3,Resistor_SMD:R_0805_2012Metric,1,fit,"Common-mode termination, centre tap to ground (AN1718 R3)",C149504
10k,R4,Resistor_SMD:R_0603_1608Metric,1,fit,RESET_N pull-up: a floating host GPIO during ESP32 boot must not hold the PHY in reset,C25804
10k,R5,Resistor_SMD:R_0603_1608Metric,1,fit,SPI CS_N pull-up,C25804
10k,R6,Resistor_SMD:R_0603_1608Metric,1,fit,IRQ_N pull-up (open-drain capable interrupt output),C25804
12k4 1%,R7,Resistor_SMD:R_0603_1608Metric,1,fit,RBIAS. 12.4 kohm 1% over the whole operating temperature range - no substitutions (data sheet).,C22865
PPS,TP1,TestPoint:TestPoint_Pad_D1.5mm,1,fit,"PPS from the LAN8651 (DIOA4): a scope probe point, also on header 13 (IO40)",
LAN8651,U1,t1s_hat:TQFN-32-1EP_5x5mm_P0.5mm_EP3.4x3.4mm_ThermalVias_SplitPaste,1,fit,"Microchip LAN8651 10BASE-T1S MAC-PHY, OPEN Alliance TC6 SPI, 32-VQFN 5x5 (internal 1.8 V core LDO -> single 3.3 V rail)",C22386973
25.000MHz CL12,Y1,Crystal:Crystal_SMD_3225-4Pin_3.2x2.5mm,1,fit,"25.000 MHz fundamental crystal, CL 12 pF, ESR 50 ohm max, SMD3225-4P - YXC X322525MOB4SI. No series or feedback resistor (data sheet).",C9006

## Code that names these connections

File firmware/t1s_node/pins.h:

// Where the T1S HAT's six host signals land on the T-ETH-Elite's ESP32-S3.
//
// Read off LilyGo's own schematic (schematic/T-ETH-ELite.pdf, sheet 2, J1), not the Pi
// pinout: the HAT was laid out to TSN Lab's Raspberry Pi device-tree overlay, so each
// signal sits on the header pin a Pi would use, and this table is what the Elite has
// wired to those pins.
//
//   HAT signal      header pin   Pi name          Elite
//   SDI  (MOSI)     19           GPIO10 MOSI      IO11  SPI_MOSI  (shared with the TF card)
//   SDO  (MISO)     21           GPIO9  MISO      IO9   SPI_MISO  (shared with the TF card)
//   SCLK            23           GPIO11 SCLK      IO10  SPI_SCLK  (shared with the TF card)
//   CS_N            24           GPIO8  CE0       IO0   BOOT      <-- strapping pin, see below
//   CS_N (Rev D)    27           GPIO0  ID_SD     IO8             moved off the strap
//   1PPS (Rev D)    13           GPIO27           IO40            LAN8651 DIOA4, also test pad TP1
//   IRQ_N           16           GPIO23           IO39
//   RESET_N         15           GPIO22           IO42
//
// CS_N on IO0. That is where the Pi convention puts CE0, and on the Elite pin 24 is the
// BOOT line. It works: the strap wants IO0 high at reset, the Elite pulls it up (R1 10k)
// and so does the HAT (R5 10k), and the LAN8651's CS_N is an input, so nothing on the HAT
// can pull it low. Two consequences that are real, though:
//   - pressing the Elite's BOOT button while running asserts CS_N and corrupts whatever
//     transaction is on the wire. The driver sees a parity error and retries; do not
//     press it on a live bus.
//   - holding BOOT at power-up still enters the ROM downloader as usual. Flashing is
//     unaffected.
//
// Rev D of this HAT moved CS_N to header 27 (IO8) and brings the LAN8651's dedicated 1PPS
// (DIOA4) to header 13 (IO40). The firmware reads DEVID on each CS candidate at boot, so
// one image runs on either board, and it knows from that which board it is on.
//
// The three bus pins are the Elite's general SPI, which also runs the TF card slot
// (CS IO12). The card is deselected at boot (kPinSdCs driven high) so it cannot answer
// on the LAN8651's transactions; using the card at the same time would need a shared
// spi bus handle, which this firmware does not do.
//
// The Elite's own W5500 is on a separate bus (IO47/21/48/45) and is untouched here.
#pragma once

constexpr int kPinT1sMosi = 11;
constexpr int kPinT1sMiso = 9;
constexpr int kPinT1sSclk = 10;
constexpr int kPinT1sCs = 0;      // Rev C / TSN Lab HAT
constexpr int kPinT1sCsRevD = 8;  // Rev D
constexpr int kPinT1sPps = 40;    // Rev D: DIOA4 1PPS in
constexpr int kPinT1sIrq = 39;
constexpr int kPinT1sReset = 42;

constexpr int kPinSdCs = 12;    // TF card chip select on the same bus -- held high
constexpr int kPinBoardLed = 38; // Elite's green LED (header pin 18)

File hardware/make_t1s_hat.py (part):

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RPI_NAMES = {
    1: "3V3", 2: "5V", 3: "GPIO2/SDA1", 4: "5V", 5: "GPIO3/SCL1", 6: "GND",
    7: "GPIO4", 8: "GPIO14/TXD", 9: "GND", 10: "GPIO15/RXD", 11: "GPIO17",
    12: "GPIO18", 13: "GPIO27", 14: "GND", 15: "GPIO22", 16: "GPIO23",
    17: "3V3", 18: "GPIO24", 19: "GPIO10/MOSI", 20: "GND", 21: "GPIO9/MISO",
    22: "GPIO25", 23: "GPIO11/SCLK", 24: "GPIO8/CE0", 25: "GND",
    26: "GPIO7/CE1", 27: "ID_SD", 28: "ID_SC", 29: "GPIO5", 30: "GND",
    31: "GPIO6", 32: "GPIO12", 33: "GPIO13", 34: "GND", 35: "GPIO19",
    36: "GPIO16", 37: "GPIO26", 38: "GPIO20", 39: "GND", 40: "GPIO21",
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     {1: "VDDP_17", 2: "GND"}, (34.6, 17.3, 0), (135.0, 45.0),
     descr="VDDP (pin 17) decoupling, 0.01 uF - closest to the pin")
# Rev C review fix: C11/C12 sit at the top-left corner of U1, fed by a B.Cu hop
# from pin 29 that passes under the TRXP/TRXN escapes BELOW the choke void (In1
# ground lies between).  Rev C as first drawn rose at x 33 and reached C12 after
# ~6.5 mm; the top-right corner now belongs to VDDAU, RBIAS and the crystal.
part("C11", "Device:C", "100nF", FP_C0603,
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# --- host-side pull-ups ----------------------------------------------------
part("R4", "Device:R", "10k", FP_R0603,
     {1: "+3V3", 2: "RESET_N"}, (22.9, 16.2, 0), (95.0, 95.0),
     descr="RESET_N pull-up: a floating host GPIO during ESP32 boot must not "
           "hold the PHY in reset")
# The three pull-ups sit on their signal where it reaches the header, so none
# of them costs a via of its own: R4 and R6 in-line on F.Cu, R5 straight onto
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    # crystal lid: each GND pad its own via (pad 4 above, pad 2 shares R7's)
    R(("GND", WF, [("Y1", "4"), (35.33, 29.05)]))
    G(("GND", 35.33, 29.05, 0.45, 0.25))
    # VDDA (29): one via beside the pin, B.Cu to the left UNDER the TRXP/TRXN
    # escapes (y 23.95, 0.45 mm below the CMC void), up again at C12.
    R(("VDDA", WQ, [("U1", "29"), (29.75, 23.40)]))
    G(("VDDA", 29.75, 23.40, 0.45, 0.25))
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    G(("+3V3", 36.30, 14.10, 0.45, 0.25))
    # DIOA0..3 (18, 19, 20, 22) are unused and go to ground (data sheet); DIOA4 (23) is PPS since Rev D.
    # Rev C review fix: they tie INWARD to the exposed pad, like pins 2/3/5, so
    # the right edge is free for CCOMP: C5 (100 nF) 1.4 mm from pin 21, C4
    # (4.7 uF) beside it, each with its own ground via.
    for pin, y in (("18", 18.75), ("19", 19.25), ("20", 19.75),
                   ("22", 20.75)):
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    R(("CCOMP", WF, [("U1", "21"), ("C5", "1")]))
    R(("CCOMP", 0.40, [("C5", "1"), ("C4", "1")]))

    # ================= QFN left edge: VDDP (pins 4, 7) and RESET_N ======
    # 0.01 uF (C8) then 0.1 uF (C7) straight off pin 7, FB3 behind them from
    # the +3V3 plane.  TEST (pin 4) must sit at VDDP; it joins pin 7 outboard
    # of the pads (pins 5/6 between carry no outward stub).
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    # J1 (pins 15-24), reachable from the top once the socket is soldered.
    # Labelling them is the test-point set the LAN8650/1 checklist asks for,
    # without new copper on a signal path.
    # Rev D: CS moved off pin 24 (IO0, the BOOT strap) to pin 27 (IO8); PPS (DIOA4) on pin 13 (IO40).
    for pin, txt in ((13, "PPS"), (15, "RST"), (17, "3V3"), (19, "MOSI"), (21, "MISO"), (23, "SCK"),
                     (27, "CS")):
        x, y = pin_xy(pin)
        add_text(board, txt, x, y + 2.10, h=0.8, w=0.62, th=0.13)   # clear of J1's outline (+1.33)
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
